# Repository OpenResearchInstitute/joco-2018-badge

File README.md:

# joco-2018-badge

Code and documentation for the unofficial electronic badge for the JoCo Cruise 2018.

This is based on the excellent work that the AND!XOR team produced for the DEFCON 25 Bender Badge.

All code and hardware design files are closed until Feb 26th, 2018 and then are licensed under the Apache license 2.0 unless superceded by notices in individual files or directories.

## Getting Started

Some resources must be installed outside of this source tree. One of these is the Nordic SDK.

Choose a place to install these on your file system. For example, we'll use "/src/joco-support/".

Download the version 12.3 of the Nordic SDK [from here](https://developer.nordicsemi.com/nRF5_SDK/nRF5_SDK_v12.x.x/nRF5_SDK_12.3.0_d7731ad.zip) and unzip it into the directory you chose.

It's known that later versions of the SDK are not compatible with the existing badge code. We may work on fixing that, which is why we don't install the SDK in the source tree for the project.

Now edit your shell init or rc file to set the following environment variable when you create a shell, substituting your chosen path:

```
export SDK_ROOT=/src/joco-support/nRF5_SDK_12.3.0_d7731ad
```

### Ubuntu Installation (non-ARM host)

Download the GNU ARM Embedded Toolchain. Choose one of these methods:

* Download the latest from <https://developer.arm.com/open-source/gnu-toolchain/gnu-rm/downloads> and unpack it into its own directory in `/usr/local`. Or,

* Download the version that Nordic used to test their SDK, 4.9 2015q3, from <https://launchpad.net/gcc-arm-embedded/+milestone/4.9-2015-q3-update> and unpack it into its own directory in `/usr/local`. Or,

* `sudo apt-get install gcc-arm-none-eabi` and take your chances on whatever version is current for your Linux. This may be your only option if you're running Linux on a non-x86 platform.

Then edit `$SDK_ROOT/components/toolchain/gcc/Makefile.posix` and change the value for `GNU_INSTALL_ROOT` to the directory where your toolchain was installed.

If you plan to hook up hardware for programming and debugging, you'll need the Segger JLink software. It's available from <https://www.segger.com/downloads/jlink/> for a variety of host platforms. We used version V6.18b, but the latest version is probably fine. To install on Ubuntu on an Intel PC:

`sudo dpkg -i <path-to-downloads>/JLink_Linux_V618b_x86_64.deb`

You'll also need a couple of command line tools from Nordic. These are available from <http://infocenter.nordicsemi.com/topic/com.nordic.infocenter.tools/dita/tools/nrf5x_command_line_tools/nrf5x_installation.html?cp=5_1_1>. We used version 9.7.0, but the latest version is probably fine. Install them in a location outside this project, like the Nordic SDK. For example using the location "/src/joco-support", you can do the following:

```
mkdir -p /src/joco-support/bin
cd /src/joco-support/bin
tar xvf <path-to-downloads>/nRF5x-Command-Line-Tools_9_7_0_Linux-x86_64.tar
```

Now edit your shell init or rc file to set the following environment variable when you create a shell, substituting your chosen path:

```
export NRFJ_BIN=/src/joco-support/bin
```

#### Ubuntu on an ARM Host

If you want to develop on an ARM-based host, most of the components are available.

The Nordic SDK is the same.

You should be able to `sudo apt-get install gcc-arm-none-eabi` to get the toolchain.

You can get JLink software [from Segger here](https://www.segger.com/downloads/jlink/#J-LinkSoftwareAndDocumentationPack)

The command line tools nrfjprog and mergehex are not currently available for ARM hosts. You can use the JLink tools to program the device, so you can probably work around nrfjprog.

### Build the code

`cd firmware/manbearpig`

`make`

`cd ..`

`./update.sh`

### JTAG interface hardware

To flash the code to the badge and use the Ozone debugger, you'll need a JTAG hardware interface.
The one that was used by the development team is the Segger [J-Link EDU Mini](https://www.segger.com/products/debug-probes/j-link/models/j-link-edu-mini/).

It's much easier to connect to the board if you use a short flat cable and a mating header on the board end. All these can be purchased from these retailers:

* [J-Link EDU Min from Adafruit](https://www.adafruit.com/product/3571)
* [Ten pin JTAG cable from Adafruit](https://www.adafruit.com/product/1675) (not the same as the one that comes with the debugger)
* [Header from Mouser](https://www.mouser.com/ProductDetail/Harwin/M50-3500542?qs=9fQaSFfsqsyXI0P9tFOVoQ%3D%3D)

### Flashing the target

Two ways, either:

`cd firmware`

`./provision.sh`

or

`cd firmware/manbearpig`

`make flash_softdevice`

`make flash`

The `make flash_softdevice` can be omitted after the first time.

### Setting up the Segger Ozone debugger

This was correct for Ubuntu 14.04.5 64 bit

Install the Ozone package [from here](https://www.segger.com/downloads/jlink/#Ozone)

The manual is useful (same link)

IMPORTANT NOTE: 

Ozone version 2.56 would not work for me. It would halt execution in seemingly random places and not load source code.

Version 2.54b works fine

If you're using the Segger edu device, Select the device as Nordic nRF52832_xxAA

Choose SWD for the debugger device and NOT USB.

open the badge .out file to bring in source files

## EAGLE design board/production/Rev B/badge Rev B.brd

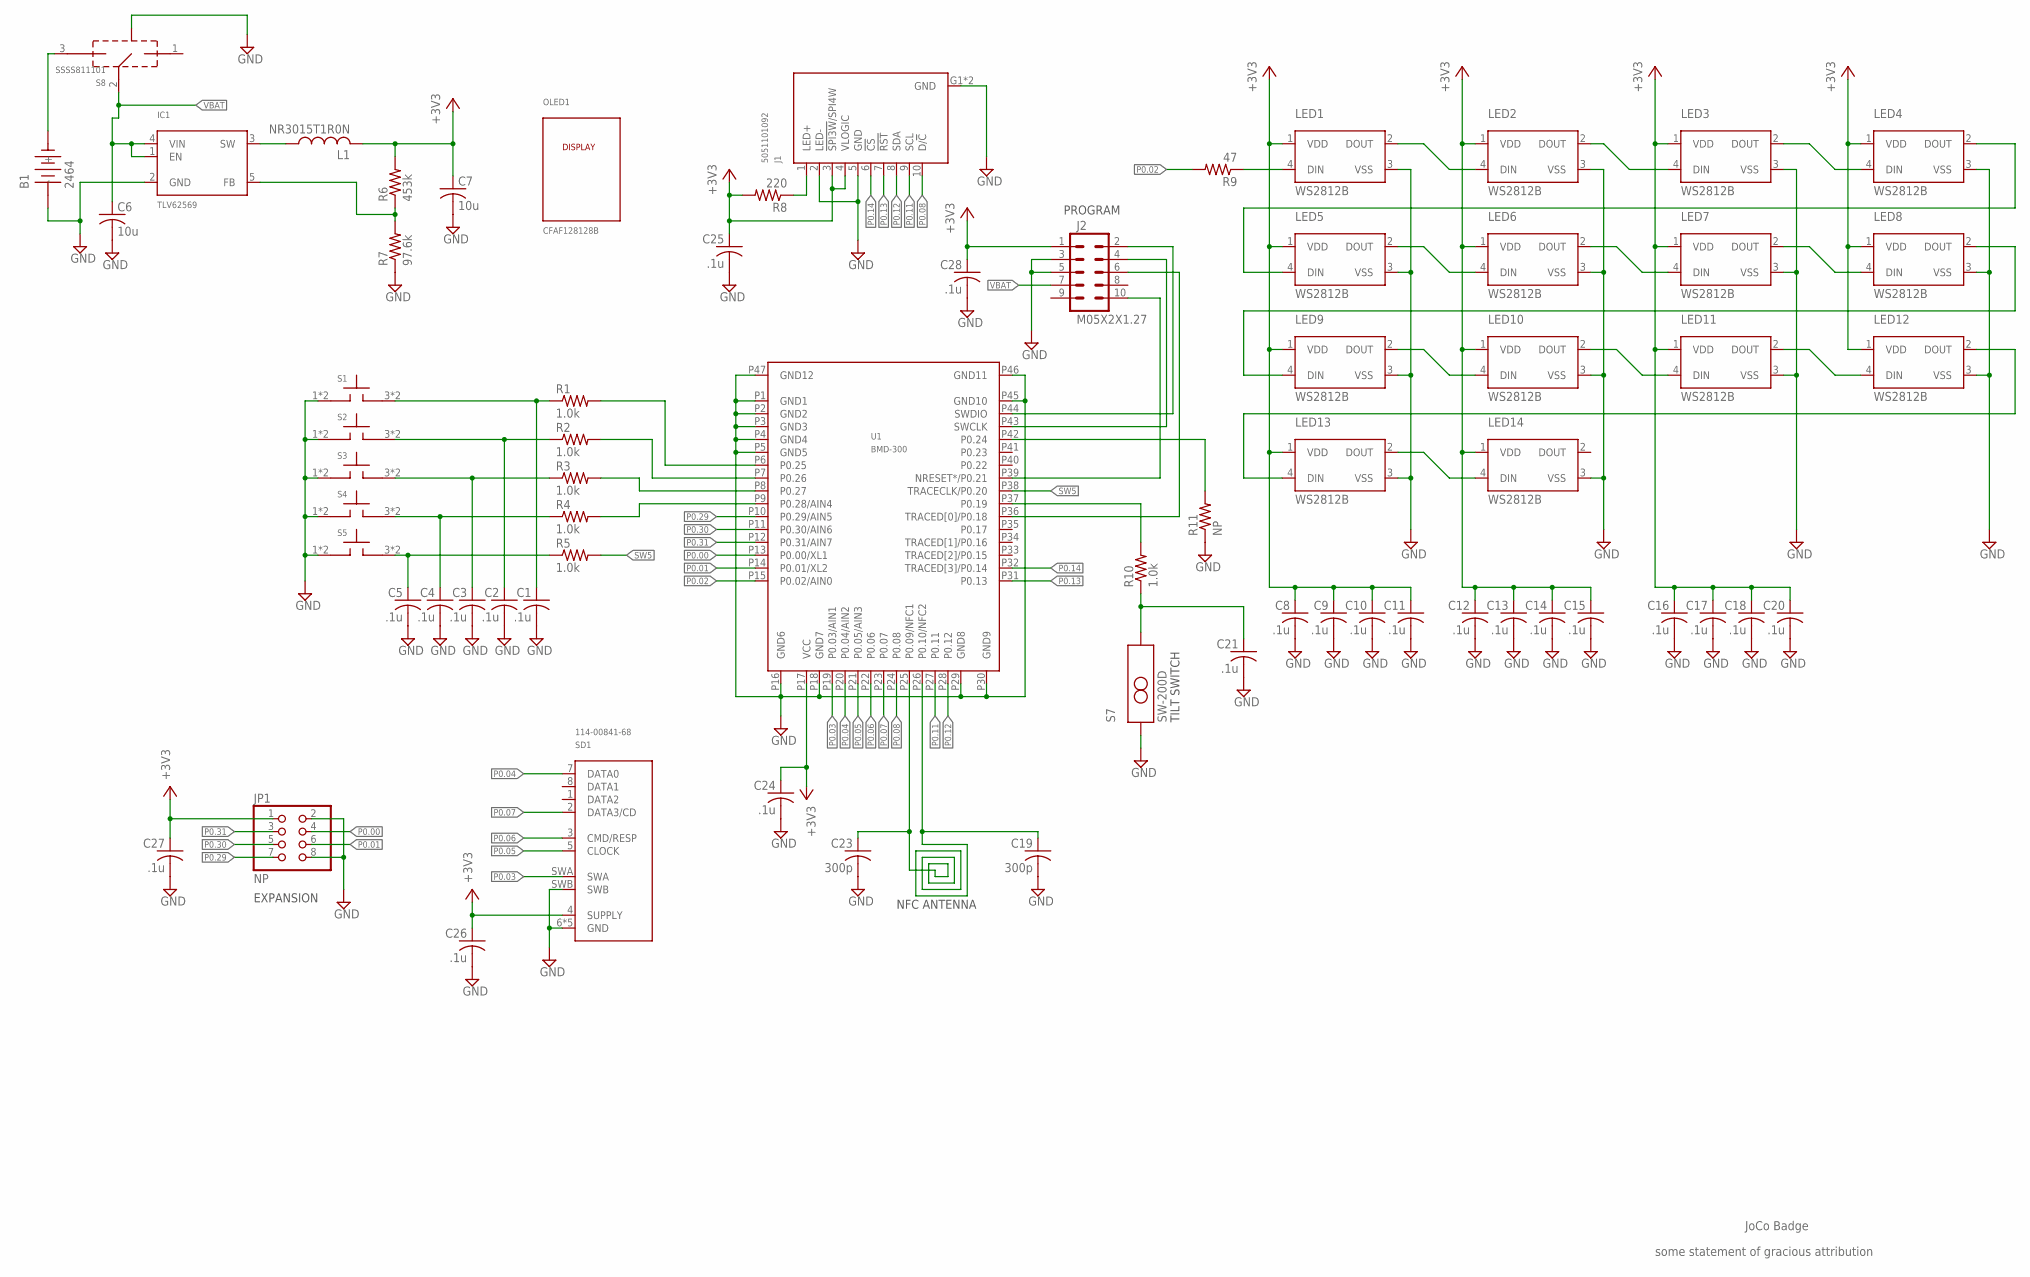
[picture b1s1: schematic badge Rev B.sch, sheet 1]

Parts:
B1: 2464
C1, C2, C3, C4, C5, C8, C9, C10, C11, C12, C13, C14, C15, C16, C17, C18, C20, C21, C24, C25, C26, C27, C28: .1u; C0402K
C6, C7: 10u; C0805K; MPN JMK212BJ106KD-T
C19, C23: 300p; C0603K
IC1: TLV62569; DBV-5
J1: 5051101092
J2: M05X2X1.27; 2X5X1.27
JP1: NP; 2X04
L1: NR3015T1R0N; NR3015
LED1, LED2, LED3, LED4, LED5, LED6, LED7, LED8, LED9, LED10, LED11, LED12, LED13, LED14: WS2812B
OLED1: CFAF128128B
R1, R2, R3, R4, R5, R10: 1.0k; R0603
R6: 453k; R0603
R7: 97.6k; R0603
R8: 220; R0603
R9: 47; R0603
R11: NP; R0805
S1, S2, S3, S4, S5: PTS810
S7: SW-200D
S8: SSSS811101
SD1: 114-00841-68
U1: BMD-300

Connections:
!RESET: J2.10, U1.P39 (NRESET*/P0.21)
+3V3: C7.1, C8.1, C9.1, C10.1, C11.1, C12.1, C13.1, C14.1, C15.1, C16.1, C17.1, C18.1, C20.1, C24.1, C25.1, C26.1, C27.1, C28.1, J1.3 (!SPI3W!/SPI4W), J1.4 (VLOGIC), J2.1, JP1.1, L1.2, LED1.1 (VDD), LED2.1 (VDD), LED3.1 (VDD), LED4.1 (VDD), LED5.1 (VDD), LED6.1 (VDD), LED7.1 (VDD), LED8.1 (VDD), LED9.1 (VDD), LED10.1 (VDD), LED11.1 (VDD), LED12.1 (VDD), LED13.1 (VDD), LED14.1 (VDD), R6.2, R8.2, SD1.4 (SUPPLY), U1.P17 (VCC)
ANT: C19.1, C23.1, U1.P25 (P0.09/NFC1), U1.P26 (P0.10/NFC2)
FB: IC1.5 (FB), R6.1, R7.2
GND: B1.-, C1.2, C2.2, C3.2, C4.2, C5.2, C6.2, C7.2, C8.2, C9.2, C10.2, C11.2, C12.2, C13.2, C14.2, C15.2, C16.2, C17.2, C18.2, C19.2, C20.2, C21.2, C23.2, C24.2, C25.2, C26.2, C27.2, C28.2, IC1.2 (GND), J1.2 (LED-), J1.5 (GND), J1.G1 (GND), J1.G2 (GND), J2.3, J2.5, JP1.2, JP1.8, LED1.3 (VSS), LED2.3 (VSS), LED3.3 (VSS), LED4.3 (VSS), LED5.3 (VSS), LED6.3 (VSS), LED7.3 (VSS), LED8.3 (VSS), LED9.3 (VSS), LED10.3 (VSS), LED11.3 (VSS), LED12.3 (VSS), LED13.3 (VSS), LED14.3 (VSS), R7.1, R11.1, S1.1 (A), S1.2 (A), S2.1 (A), S2.2 (A), S3.1 (A), S3.2 (A), S4.1 (A), S4.2 (A), S5.1 (A), S5.2 (A), S7.A, S8.G1 (GND), S8.G2 (GND), S8.G3 (GND), S8.G4 (GND), SD1.6 (GND), SD1.G1 (GND), SD1.G2 (GND), SD1.G3 (GND), SD1.G4 (GND), SD1.SWB, U1.P1 (GND1), U1.P2 (GND2), U1.P3 (GND3), U1.P4 (GND4), U1.P5 (GND5), U1.P16 (GND6), U1.P18 (GND7), U1.P29 (GND8), U1.P30 (GND9), U1.P45 (GND10), U1.P46 (GND11), U1.P47 (GND12)
unnamed: C1.1, R1.1, S1.3 (B), S1.4 (B)
unnamed: C2.1, R2.1, S2.3 (B), S2.4 (B)
unnamed: C3.1, R3.1, S3.3 (B), S3.4 (B)
unnamed: C4.1, R4.1, S4.3 (B), S4.4 (B)
unnamed: C5.1, R5.1, S5.3 (B), S5.4 (B)
unnamed: R1.2, U1.P6 (P0.25)
unnamed: R2.2, U1.P7 (P0.26)
unnamed: R3.2, U1.P8 (P0.27)
unnamed: R4.2, U1.P9 (P0.28/AIN4)
unnamed: R11.2, U1.P42 (P0.24)
unnamed: C21.1, R10.1, S7.C
unnamed: J1.1 (LED+), R8.1
unnamed: LED5.2 (DOUT), LED6.4 (DIN)
unnamed: LED9.2 (DOUT), LED10.4 (DIN)
unnamed: LED13.2 (DOUT), LED14.4 (DIN)
unnamed: LED1.2 (DOUT), LED2.4 (DIN)
unnamed: LED6.2 (DOUT), LED7.4 (DIN)
unnamed: LED10.2 (DOUT), LED11.4 (DIN)
unnamed: LED3.2 (DOUT), LED4.4 (DIN)
unnamed: LED7.2 (DOUT), LED8.4 (DIN)
unnamed: LED2.2 (DOUT), LED3.4 (DIN)
unnamed: LED11.2 (DOUT), LED12.4 (DIN)
unnamed: LED4.2 (DOUT), LED5.4 (DIN)
unnamed: LED8.2 (DOUT), LED9.4 (DIN)
unnamed: LED12.2 (DOUT), LED13.4 (DIN)
unnamed: LED1.4 (DIN), R9.1
P0.00: JP1.4, U1.P13 (P0.00/XL1)
P0.01: JP1.6, U1.P14 (P0.01/XL2)
P0.02: R9.2, U1.P15 (P0.02/AIN0)
P0.03: SD1.SWA, U1.P19 (P0.03/AIN1)
P0.04: SD1.7 (DATA0), U1.P20 (P0.04/AIN2)
P0.05: SD1.5 (CLOCK), U1.P21 (P0.05/AIN3)
P0.06: SD1.3 (CMD/RESP), U1.P22 (P0.06)
P0.07: SD1.2 (DATA3/CD), U1.P23 (P0.07)
P0.08: J1.10 (D/!C), U1.P24 (P0.08)
P0.11: J1.9 (SCL), U1.P27 (P0.11)
P0.12: J1.8 (SDA), U1.P28 (P0.12)
P0.13: J1.7 (!RST), U1.P31 (P0.13)
P0.14: J1.6 (!CS), U1.P32 (TRACED[3]/P0.14)
P0.18: J2.6, U1.P36 (TRACED[0]/P0.18)
P0.19: R10.2, U1.P37 (P0.19)
P0.29: JP1.7, U1.P10 (P0.29/AIN5)
P0.30: JP1.5, U1.P11 (P0.30/AIN6)
P0.31: JP1.3, U1.P12 (P0.31/AIN7)
SW: IC1.3 (SW), L1.1
SW5: R5.2, U1.P38 (TRACECLK/P0.20)
SWCLK: J2.4, U1.P43 (SWCLK)
SWDIO: J2.2, U1.P44 (SWDIO)
VBAT: C6.1, IC1.1 (EN), IC1.4 (VIN), J2.7, S8.2
VIN: B1.+, S8.3

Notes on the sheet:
some statement of gracious attribution
JoCo Badge
TILT SWITCH
NFC ANTENNA
EXPANSION
PROGRAM

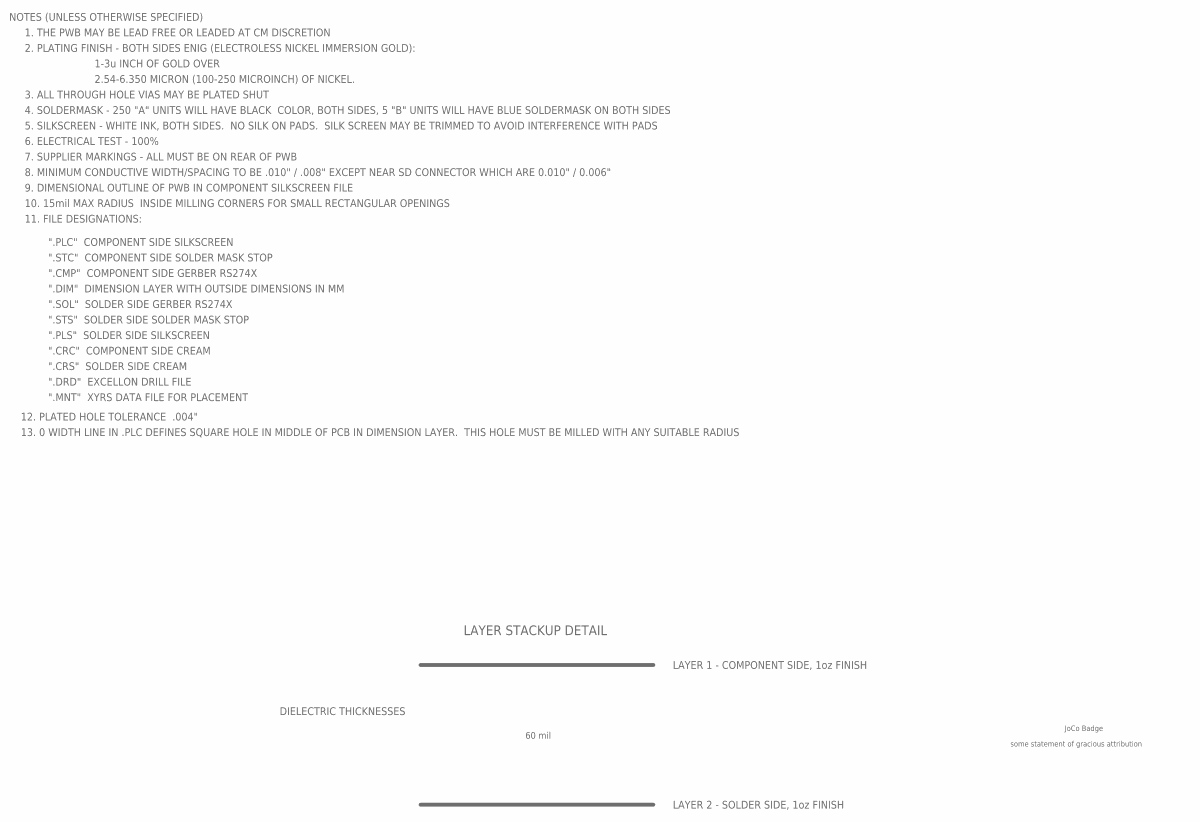
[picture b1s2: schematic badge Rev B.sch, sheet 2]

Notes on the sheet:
some statement of gracious attribution
JoCo Badge
NOTES (UNLESS OTHERWISE SPECIFIED)
1. THE PWB MAY BE LEAD FREE OR LEADED AT CM DISCRETION
2. PLATING FINISH - BOTH SIDES ENIG (ELECTROLESS NICKEL IMMERSION GOLD):
1-3u INCH OF GOLD OVER
2.54-6.350 MICRON (100-250 MICROINCH) OF NICKEL.
3. ALL THROUGH HOLE VIAS MAY BE PLATED SHUT
4. SOLDERMASK - 250 "A" UNITS WILL HAVE BLACK COLOR, BOTH SIDES, 5 "B" UNITS WILL HAVE BLUE SOLDERMASK ON BOTH SIDES
5. SILKSCREEN - WHITE INK, BOTH SIDES. NO SILK ON PADS. SILK SCREEN MAY BE TRIMMED TO AVOID INTERFERENCE WITH PADS
6. ELECTRICAL TEST - 100%
7. SUPPLIER MARKINGS - ALL MUST BE ON REAR OF PWB
8. MINIMUM CONDUCTIVE WIDTH/SPACING TO BE .010" / .008" EXCEPT NEAR SD CONNECTOR WHICH ARE 0.010" / 0.006"
9. DIMENSIONAL OUTLINE OF PWB IN COMPONENT SILKSCREEN FILE
11. FILE DESIGNATIONS:
".CMP" COMPONENT SIDE GERBER RS274X
".SOL" SOLDER SIDE GERBER RS274X
".PLC" COMPONENT SIDE SILKSCREEN
".PLS" SOLDER SIDE SILKSCREEN
".CRC" COMPONENT SIDE CREAM
".CRS" SOLDER SIDE CREAM
".STC" COMPONENT SIDE SOLDER MASK STOP
".STS" SOLDER SIDE SOLDER MASK STOP
".DRD" EXCELLON DRILL FILE
".MNT" XYRS DATA FILE FOR PLACEMENT
LAYER 1 - COMPONENT SIDE, 1oz FINISH
LAYER 2 - SOLDER SIDE, 1oz FINISH
DIELECTRIC THICKNESSES
60 mil
LAYER STACKUP DETAIL
12. PLATED HOLE TOLERANCE .004"
10. 15mil MAX RADIUS INSIDE MILLING CORNERS FOR SMALL RECTANGULAR OPENINGS
".DIM" DIMENSION LAYER WITH OUTSIDE DIMENSIONS IN MM
13. 0 WIDTH LINE IN .PLC DEFINES SQUARE HOLE IN MIDDLE OF PCB IN DIMENSION LAYER. THIS HOLE MUST BE MILLED WITH ANY SUITABLE RADIUS

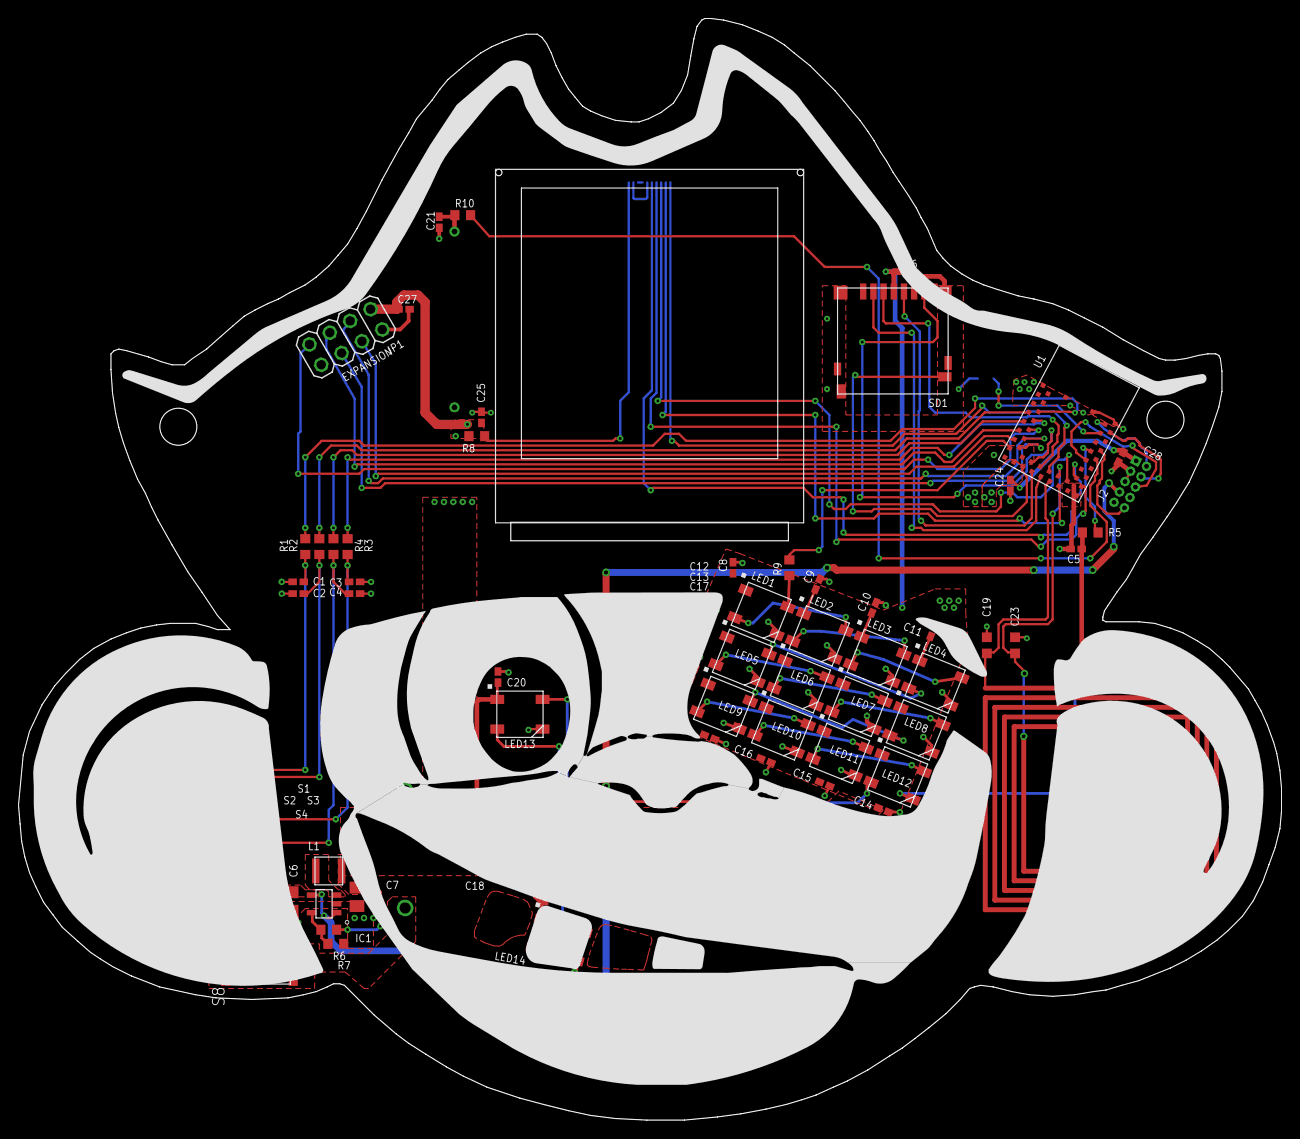
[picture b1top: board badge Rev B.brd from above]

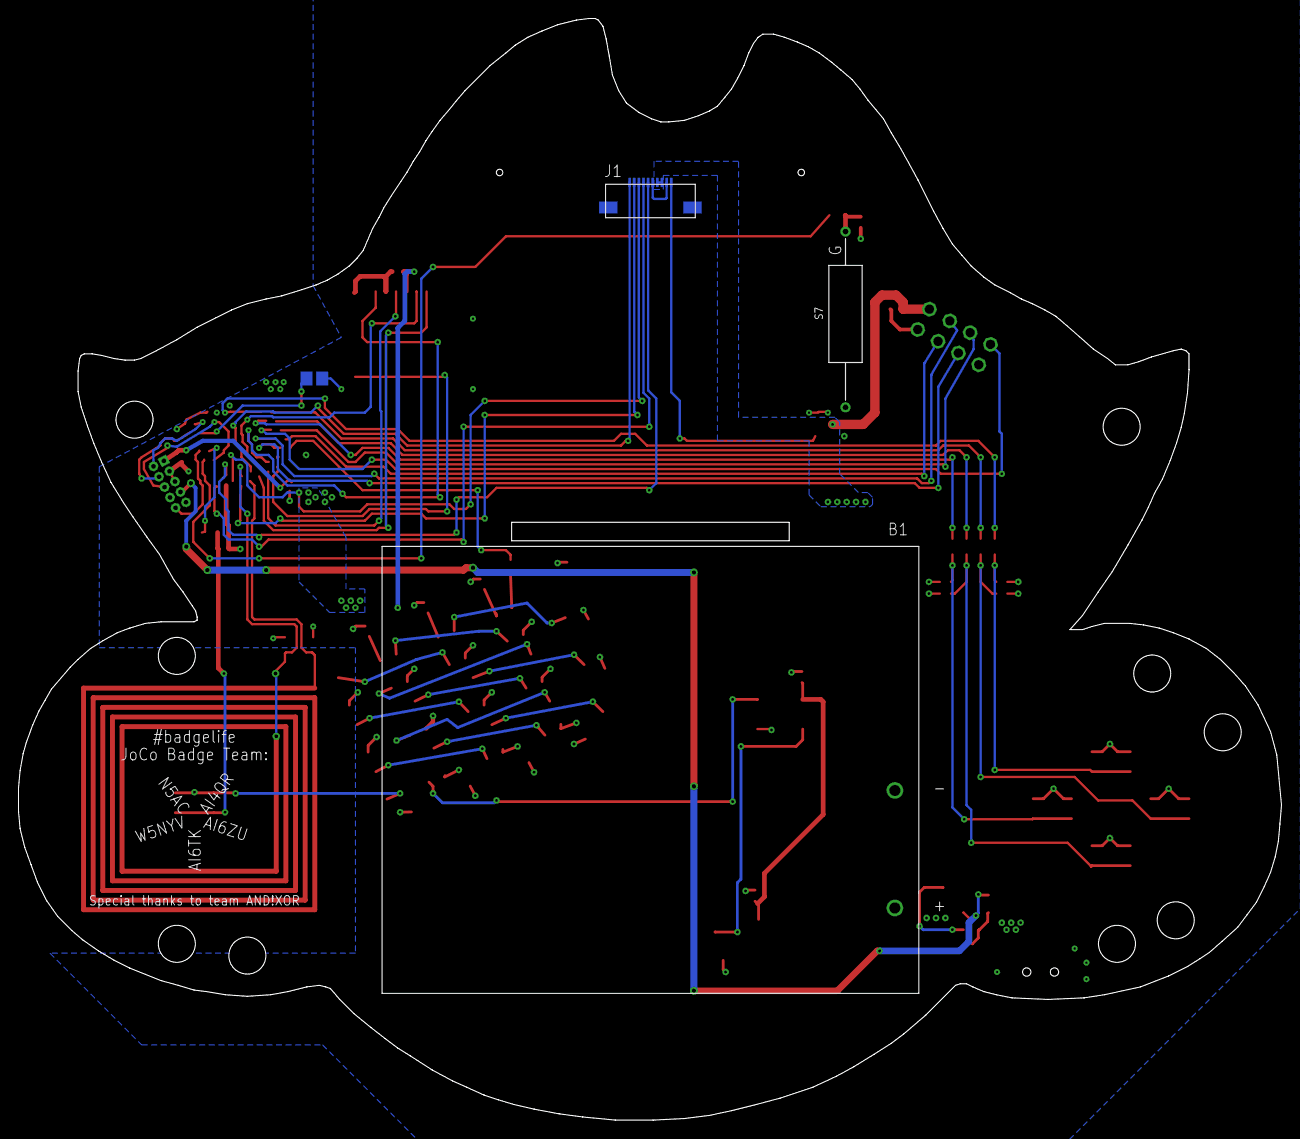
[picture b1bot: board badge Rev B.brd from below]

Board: 2 copper layers, 136.5 x 119.0 mm, 68 parts (4 on the bottom side), 55 nets.

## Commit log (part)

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2017-08-10 readme
2017-08-10 initial commit of ANDnXOR bender source
2017-08-14 Ignore a warning and clean up whitespace
    gcc is throwing a warning for using char as an array subscript even though the declaration is for uint8_t. So ignore that.
    Also, clean up lots of extra spaces and make tab use consistent
2017-08-20 Move spreadsheet to google docs, and update README
2017-08-27 Add first unfinished proto board designs
2017-08-31 more layout work
2017-08-31 unignore and add library files fro kicad
2017-09-04 lots more layout work
2017-09-05 Add rescue lib from version change
2017-09-05 Add cache.lib
2017-09-06 layout maybe finished
2017-09-12 Add final board info for proto1
2017-09-16 coverting files to Eagle, checking in data sheets
2017-09-16 added power suppy to proto2
2017-09-21 adding additional parts
2017-09-21 adding bling LEDs to proto2
2017-10-01 Remove Nordic SDK from the repo, add instructions.
    In order to make it cleaner to switch versions of the SDK,
    we no longer check the SDK into the repository.
    In order to make it easier to get started with the toolchain,
    there are now detailed instructions in README.md.
2017-10-01 Remove Nordic Command Line Tools from repo.
2017-10-01 Improve getting started instructions.
2017-10-04 Typo in SDK URL
2017-10-04 Improved Getting Started info
2017-10-06 strip out botnet code
2017-10-07 Move the SDK and platform-specific tools out of the repo
    Place the Nordic programming tools and SDK outside the git repository and use environment variables to point to them.
    This prevents having to maintain files in the local directory tree which aren't under git.
2017-10-11 Find Makefile.posix in the new location
2017-10-27 Change some defcon text to joco
2017-10-27 Make button repeat delay longer during code entry
2017-10-31 Add support for NFC
2017-11-12 adding outline of monkey to PCB
2017-11-12 silkscreen for monkey
2017-11-12 added gold teeth
2017-11-12 guides for LEDs, etc
2017-11-12 add guides for LEDs; place LEDs, battery, CPU
2017-11-12 adding original AI from Amy; board specifications (TBD)
2017-11-12 add .DS_Store to gitignore
2017-12-02 copy Amy's board revision to proto2 (change tPlace artwork)
2017-12-02 reduce LEDs to 14, add tilt switch, draw NFC antenna
2017-12-02 added expansion connector to schematic
2017-12-02 added programming cable connector
2017-12-02 add decoupling caps
2017-12-02 layout in process
2017-12-03 lots of routing going on
2017-12-03 routing almost done. I hate 2-layer PCBs
2017-12-03 goffing around with artwork
2017-12-03 change to SW-200D part
2017-12-03 remove unneeded pin labels
2017-12-04 added lanyard holes; thanks to AND\!XOR
2017-12-04 add earring holes
2017-12-05 changes for errors found by AI4QR
2017-12-16 remove Old backer bling code from firmware and files from SD card
2017-12-18 final changes to proto2, saving Gerbers
2017-12-27 Shuffle boot image and ANDNXOR backer bling
2017-12-27 change LED indices and function names for pirate monkey
2017-12-27 remove whiskey pirate clue for DC25 from the pirate bling
2017-12-27 Change various ANDnXOR menu headers and other things to JOCO2018
2017-12-28 Fix SD card omissions
2017-12-28 Fix some broken menus
2017-12-28 remove unused Bender archive from SD Card
2017-12-28 Fix LED bling for andnxor backer bling
2017-12-29 Change company ID for joco badge, update to handle interactions with bender
2017-12-29 increase menu delay to prevent double buttons
2017-12-29 Add image file tools
2017-12-29 Add Wil Wheaton bling mode
2017-12-29 Add pirate monkey boot intro image
2017-12-29 Add the readme from andnxor for the SD card
2018-01-01 move resistor out of way of display
2018-01-01 reset masks to 4mil
2018-01-01 add secret resistor
2018-01-07 remove andnxor reference and add a way to enable all bling modes easily
2018-01-07 Fix a typo in airplane mode
2018-01-07 Make tooth LED gold and flashing
2018-01-07 Change the background image for the menus to a pirate monkey one
2018-01-07 remove the ANDNXOR chip8 game
2018-01-08 move flex connector 1mm to the North
2018-01-08 move expansion connector
2018-01-08 move team and thanks position due to tild switch nove to back of board
2018-01-08 rotated SD card 180-degrees
2018-01-08 update assembly instructions for PCB
2018-01-09 change lanyard holes to 4mm
2018-01-10 WIP schematic rules
2018-01-10 change mask to blue for 5 boards
2018-01-10 swap out switch for one with better mechanical stability
2018-01-10 production board and Gerbers
2018-01-10 make note about hole in center of PCB
2018-01-20 Cropped GIFs for Bling
2018-01-20 Move new images to a new directory for source images
2018-01-20 Add more source image files
2018-01-20 Change yet anothe rbender string to joco, this time in ble
2018-01-21 Add code reading notes.
    These are notes I took while reading the AND!XOR Bender badge code,
    concentrating on particular subjects. They may or may not be useful
    for others trying to understand the code.
2018-01-21 Checked in DC25 Wall of Bender code to start Wall of Joco
2018-01-22 Add new bling modes
    Added new files to the SD card, bumped SD version
    Added new bling to the menu
    Deleted old files from SD card
2018-01-22 Resolve stack/heap crash in menu system
    Changed the menu system to cache only the icons that are visible
    on screen, instead of every icon for every menu entry. This relaxes
    the limit on how many menu items there can be, so specifically the
    custom bling menu can be much longer.
    Also installed the mechanism to control the sizes of the stack and
    the heap, in config/startup_config.h. However, the sizes currently
2018-01-26 Add for NFC payload
    Add actual content for the NFC tag emulation, consisting of a fixed text string.
2018-01-27 Update Wall of JoCo README for RTC.
2018-01-27 Update Wall of JoCo README, remove DEFCON
2018-01-27 Change the unlock constants and remap to bling for joco
    Edit the #define mask names to match what we're using them for in joco. Comment out some of the code that's used in beacon receiving to enable these, because we need to move it to be based on badge p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
2018-01-28 Add initial joco gameplay files
    Add new files and constants for game play. Add the score and last_level_dispensed to the state that gets saved.
2018-01-28 put some reasonable numbers in for RSSI
2018-01-28 Put the JoCo data we need in the BLE advertising data
    The 'level' field was repurposed to lld (last_level_dispensed)
    The 8 bit avatar field was replaces with a 16 bit score field.
    Data offsets were adjusted accordingly in the data.
    The new fields are read into the badge_db information for badges that are 'heard'
    This has not yet been tested to make sure it's sent and received correctly.
2018-01-29 Remove the rest of the badge activation code and tests
2018-01-29 change state encryption key
2018-01-30 Add code reading notes for connected mode.
2018-01-31 Merge trinket dispensing flag with score in BLE advertising
    It turns out that there was not enough room in the BLE data to add one more byte of data. By doing this, if the name is a full 8 bytes long, then it gets translated into a short naem format, and we d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
    The solution is to simply adevrtise a flag that incicates that the badge has some outstanding 'credits' for trinkets which can be dispensed. This flag is the high but of the 16 bit unsigned score val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
2018-02-01 Replace 6 calls to snprintf
    It seemed dumb to call snprintf 6 times to convert a byte array to Ascii hex, and the terminating numm that is created was wrong, so include a small function to do this task.
2018-02-01 Update BLE score on load from SD card
2018-02-01 Add basic BLE service for score and lld.
    Created a GATT service with two characteristics. One is a read-only
    struct containing the current score and last_level_dispensed. The
    other is a write-only 64-bit command code, which currently implements
    commands to set score and lld.
    Security: none yet. The read characteristic is completely public, and
    once that's spoofed it's easy to trick the station into sending you
2018-02-03 Added File Crypto Notes to codereading
2018-02-04 add db functions to store badges we've contacted/visited
2018-02-04 Make a copy to encrypt before encrypting!
2018-02-08 Crypto state and score cleanup
    Added macros in util_crypto.h to encapsulate some of the procedure for
    accessing the util_crypto routines. Changed mbp_state.c and score_ble.c
    to use them.
    Switched from separate score_set and lld_set functions to a single
    score_update function that does its own fetching of the data from the
    mbp_state database. Changed mbp_state.c to use it. The new update
2018-02-09 Add new visit tracking
    Completely rework the db/list of heard badges.
    Only joco badges that we haven't 'visited' are stored in
    the primary active list. Other badges and one's we've
    visited are stored in a second cache list, which is backed
    by the database on SD card for vistied badges.
2018-02-09 Change Scoring and joco hello bling
2018-02-10 Add a file to the DB directory so git keeps the directory
2018-02-11 Add name to NFC data
2018-02-11 Add a menu selection to view current game status
2018-02-11 Fix hello timing
    Hello timer was set using the non-local millis, and the next hello time
    was set to zero, which resulted in immediate hellos on boot before the
    splash screen even finished. Fixed this.
2018-02-11 Darker background image for joco hello bling
2018-02-11 remove some char cast warnings
2018-02-12 Add eye animation in idle mode
2018-02-13 Update NFC tag data on name change
2018-02-13 Truncate NFC data length to only used bytes
2018-02-13 Change icon for menu score entry and other improvements
    Also exit the score display on any button press.
    Bumped SD card and software version numbers.
2018-02-13 Score bling now displays the name of the otehr badge scored
2018-02-13 Reverse order of score and bling menu items
2018-02-13 Make top level game over animation loop
2018-02-14 Change global time secret so we don't take updates from Bender badges
2018-02-14 Add scoring for playing chip8 games
2018-02-14 remove chip8 demos
2018-02-14 Add name to seen list data
2018-02-14 Display nearby badges from both active and seen lists
2018-02-14 Update license text in firmware files
2018-02-14 clean up cruft in comments
2018-02-14 Fix calculation of outstanding trinkets
2018-02-15 Add Device ID to NFC packet
2018-02-15 Fix "trinkets avail" on score screen
2018-02-15 require more signal strength to score a visit
2018-02-15 Move test for seekrit jumper earlier in boot
2018-02-16 replace a couple of preview images with a black display
2018-02-16 Add some notation to the TCL README
2018-02-16 Remove unused botnet files from SD card
2018-02-16 Change README for twitter
2018-02-16 display nearby count in test screen
2018-02-16 Change the LED indices for the TCL eyes demo
2018-02-16 bump SD version for Joco copy run
2018-02-16 Fix BLE bug and kludge LLD update
2018-02-16 Version to 1.8
2018-02-16 Make score characteristic stay in user memory
2018-02-16 Update advertised LLD when trinket is dispensed
2018-02-16 Spell it "Airplne Mode" to fit on the screen
2018-02-17 Unlock all master bling for any master
2018-02-17 put Wil Wheaton bling behind a password
2018-02-17 Version and build for release
2018-02-18 fix script
2018-02-28 Add NFC reader README
2018-02-28 Add pdf of schematic
2018-03-05 Add proto1 schematic pdf
2018-04-24 Add BOM to board info
2018-04-24 Add debugger info to README
2018-04-24 Add more documentation of interest to developers
2018-04-24 fixup markdown
